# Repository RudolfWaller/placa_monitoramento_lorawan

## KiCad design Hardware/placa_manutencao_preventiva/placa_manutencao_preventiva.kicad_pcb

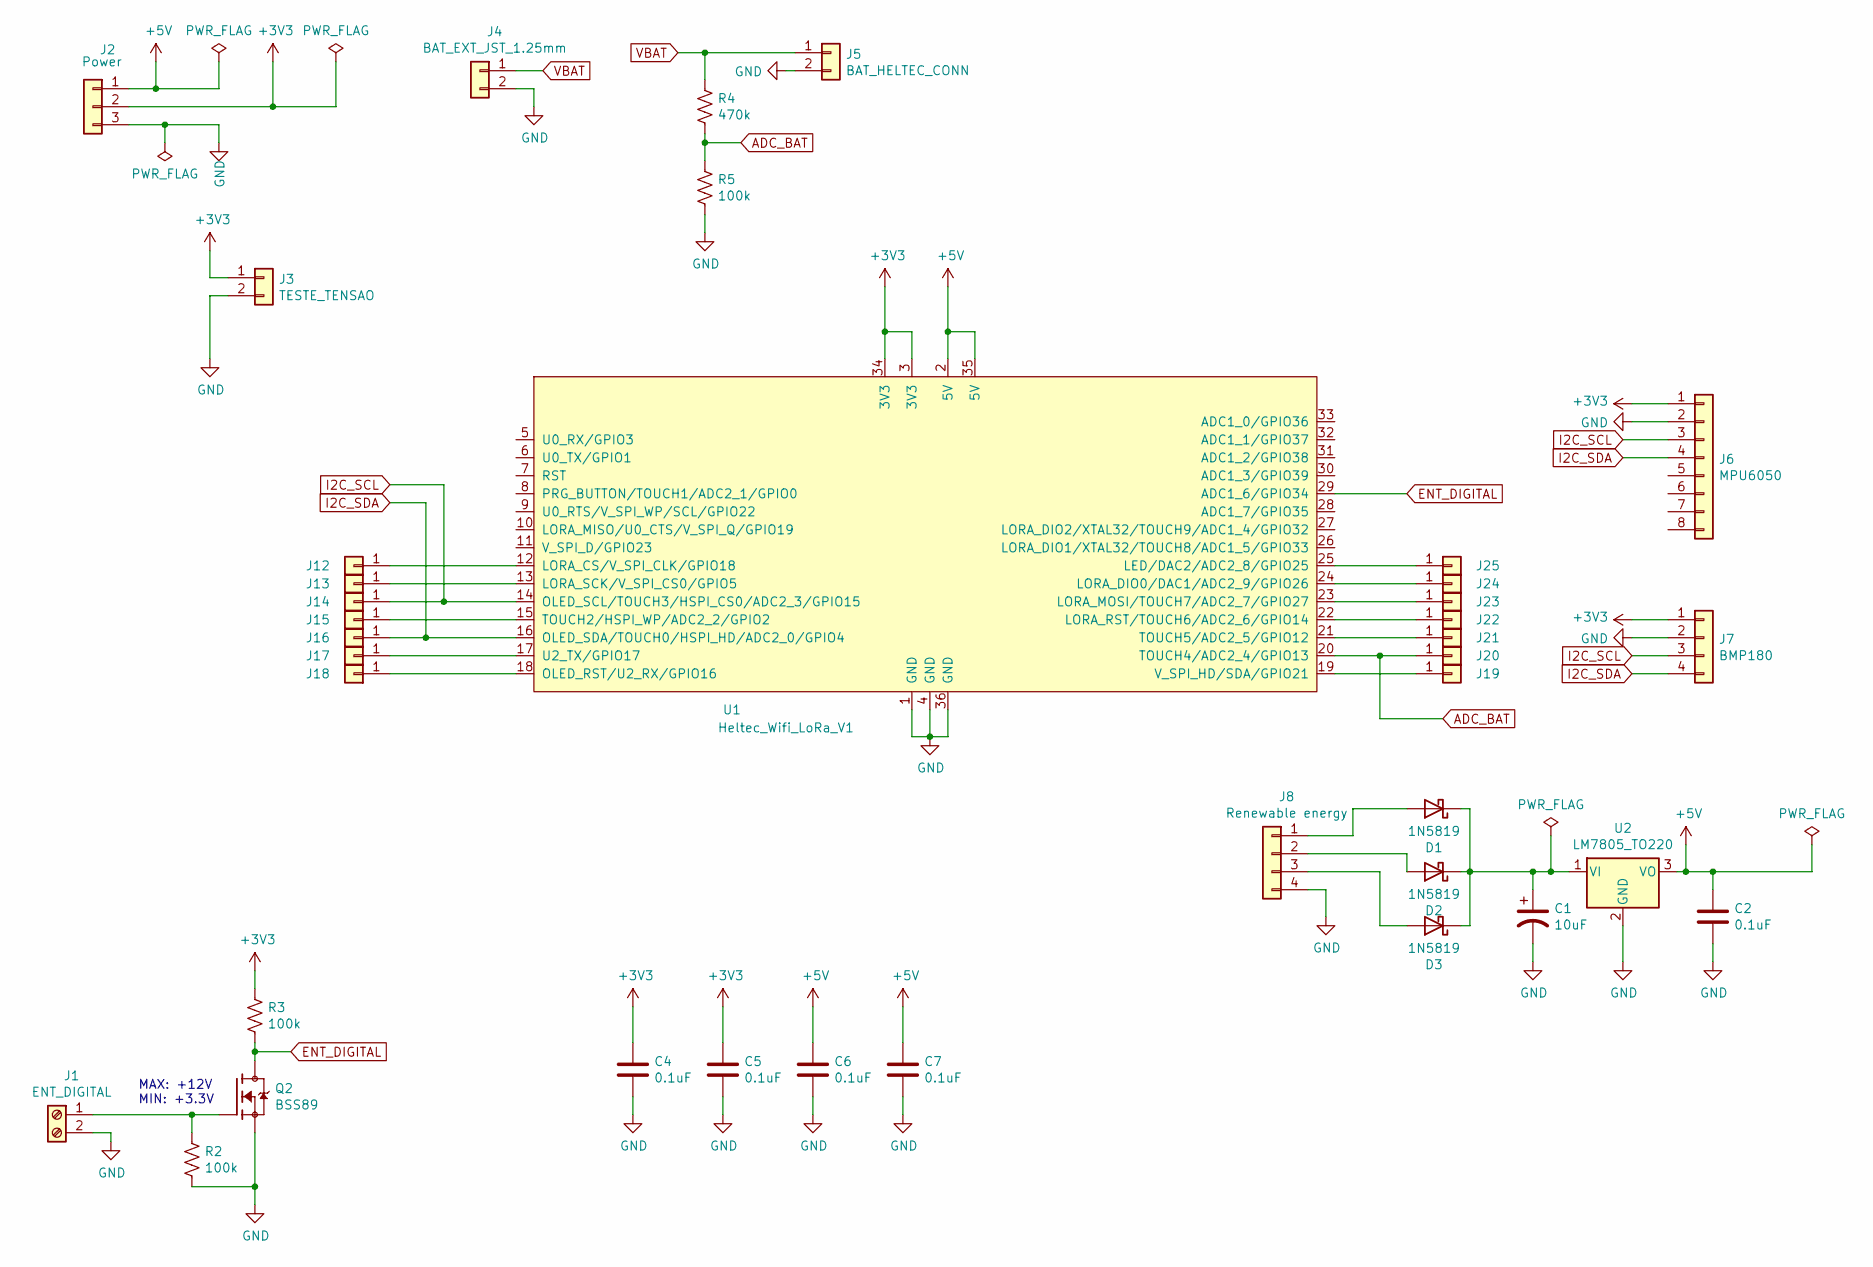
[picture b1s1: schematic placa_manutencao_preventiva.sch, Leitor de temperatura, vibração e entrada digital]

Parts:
C1: 10uF; CP_Radial_D5.0mm_P2.00mm
C2, C4, C5, C6, C7: 0.1uF; C_Disc_D5.1mm_W3.2mm_P5.00mm
D1, D2, D3: 1N5819; D_DO-41_SOD81_P10.16mm_Horizontal
J1: ENT_DIGITAL; PhoenixContact_MCV_1,5_2-G-5.08_1x02_P5.08mm_Vertical
J2: Power; PinHeader_1x03_P2.54mm_Vertical
J3: TESTE_TENSAO; TestPoint_2Pads_Pitch2.54mm_Drill0.8mm
J4: BAT_EXT_JST_1.25mm; PinHeader_1x02_P1.27mm_Vertical
J5: BAT_HELTEC_CONN; PinHeader_1x02_P2.54mm_Horizontal
J6: MPU6050; PinSocket_1x08_P2.54mm_Vertical
J7: BMP180; PinSocket_1x04_P2.54mm_Vertical
J8: Renewable energy; PinHeader_1x04_P2.54mm_Vertical
J12, J13, J14, J15, J16, J17, J18, J19, J20, J21, J22, J23, J24, J25: Conn_01x01; Pin_D0.9mm_L10.0mm_W2.4mm_FlatFork
Q2: BSS89; TO-92L_Inline
R2, R3, R5: 100k; R_Axial_DIN0207_L6.3mm_D2.5mm_P10.16mm_Horizontal
R4: 470k; R_Axial_DIN0207_L6.3mm_D2.5mm_P10.16mm_Horizontal
U1: Heltec_Wifi_LoRa_V1; Heltec_WiFi_LoRa_V1
U2: LM7805_TO220; TO-220-3_Vertical

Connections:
+3V3: C4.1, C5.1, J2.2, J3.1, J6.1, J7.1, R3.1, U1.3 (3V3), U1.34 (3V3)
+5V: C2.1, C6.1, C7.1, J2.1, U1.2 (5V), U1.35 (5V), U2.3 (VO)
ADC_BAT: J20.1, R4.2, R5.1, U1.20 (TOUCH4/ADC2_4/GPIO13)
ENT_DIGITAL: Q2.2 (D), R3.2, U1.29 (ADC1_6/GPIO34)
GND: C1.2, C2.2, C4.2, C5.2, C6.2, C7.2, J1.2, J2.3, J3.2, J4.2, J5.2, J6.2, J7.2, J8.4, Q2.1 (S), R2.2, R5.2, U1.1 (GND), U1.4 (GND), U1.36 (GND), U2.2 (GND)
I2C_SCL: J6.3, J7.3, J14.1, U1.14 (OLED_SCL/TOUCH3/HSPI_CS0/ADC2_3/GPIO15)
I2C_SDA: J6.4, J7.4, J16.1, U1.16 (OLED_SDA/TOUCH0/HSPI_HD/ADC2_0/GPIO4)
unnamed: C1.1, D1.1 (K), D2.1 (K), D3.1 (K), U2.1 (VI)
unnamed: D1.2 (A), J8.1
unnamed: D2.2 (A), J8.2
unnamed: D3.2 (A), J8.3
unnamed: J1.1, Q2.3 (G), R2.1
unnamed: J12.1, U1.12 (LORA_CS/V_SPI_CLK/GPIO18)
unnamed: J13.1, U1.13 (LORA_SCK/V_SPI_CS0/GPIO5)
unnamed: J15.1, U1.15 (TOUCH2/HSPI_WP/ADC2_2/GPIO2)
unnamed: J17.1, U1.17 (U2_TX/GPIO17)
unnamed: J18.1, U1.18 (OLED_RST/U2_RX/GPIO16)
unnamed: J19.1, U1.19 (V_SPI_HD/SDA/GPIO21)
unnamed: J21.1, U1.21 (TOUCH5/ADC2_5/GPIO12)
unnamed: J22.1, U1.22 (LORA_RST/TOUCH6/ADC2_6/GPIO14)
unnamed: J23.1, U1.23 (LORA_MOSI/TOUCH7/ADC2_7/GPIO27)
unnamed: J24.1, U1.24 (LORA_DIO0/DAC1/ADC2_9/GPIO26)
unnamed: J25.1, U1.25 (LED/DAC2/ADC2_8/GPIO25)
VBAT: J4.1, J5.1, R4.1

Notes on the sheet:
MAX: +12V MIN: +3.3V

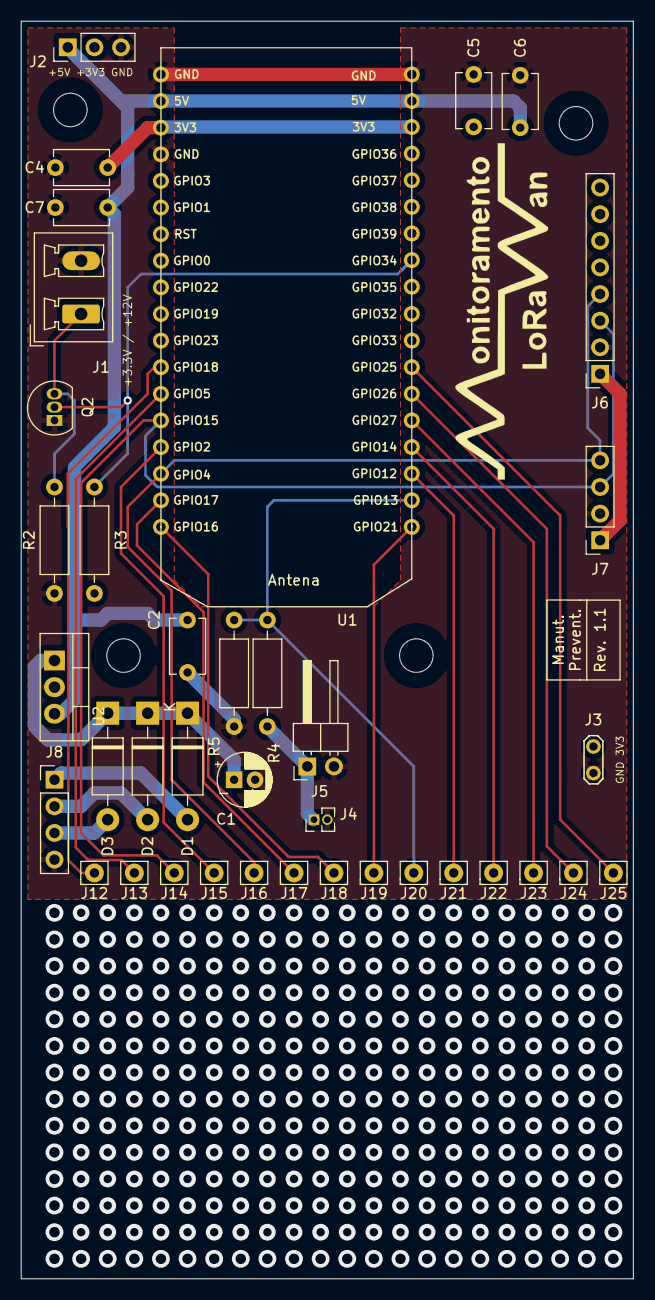
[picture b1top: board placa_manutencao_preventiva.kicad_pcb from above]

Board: 2 copper layers, 58.4 x 120.0 mm, 39 parts (0 on the bottom side), 24 nets.

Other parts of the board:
 : Arduino_UNO_R3_OnlyMountingHoles

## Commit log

2021-03-24 Substituição do mosfet para BSS-89
